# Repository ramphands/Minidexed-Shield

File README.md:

# Minidexed-Shield
A shield for a Raspberry Pi (Model 3) running [Minidexed](https://github.com/probonopd/MiniDexed/)

image of the shield in use

A Pi Pico is used as a Host to Host connection, allowing sequencing via PC or other host device.  Code obtained from [rsta2's "midi_adapter" Pico repo](https://github.com/rsta2/pico)

Please use the minixeded.ini file in this repo as the encoder pinout is different from the stock .ini

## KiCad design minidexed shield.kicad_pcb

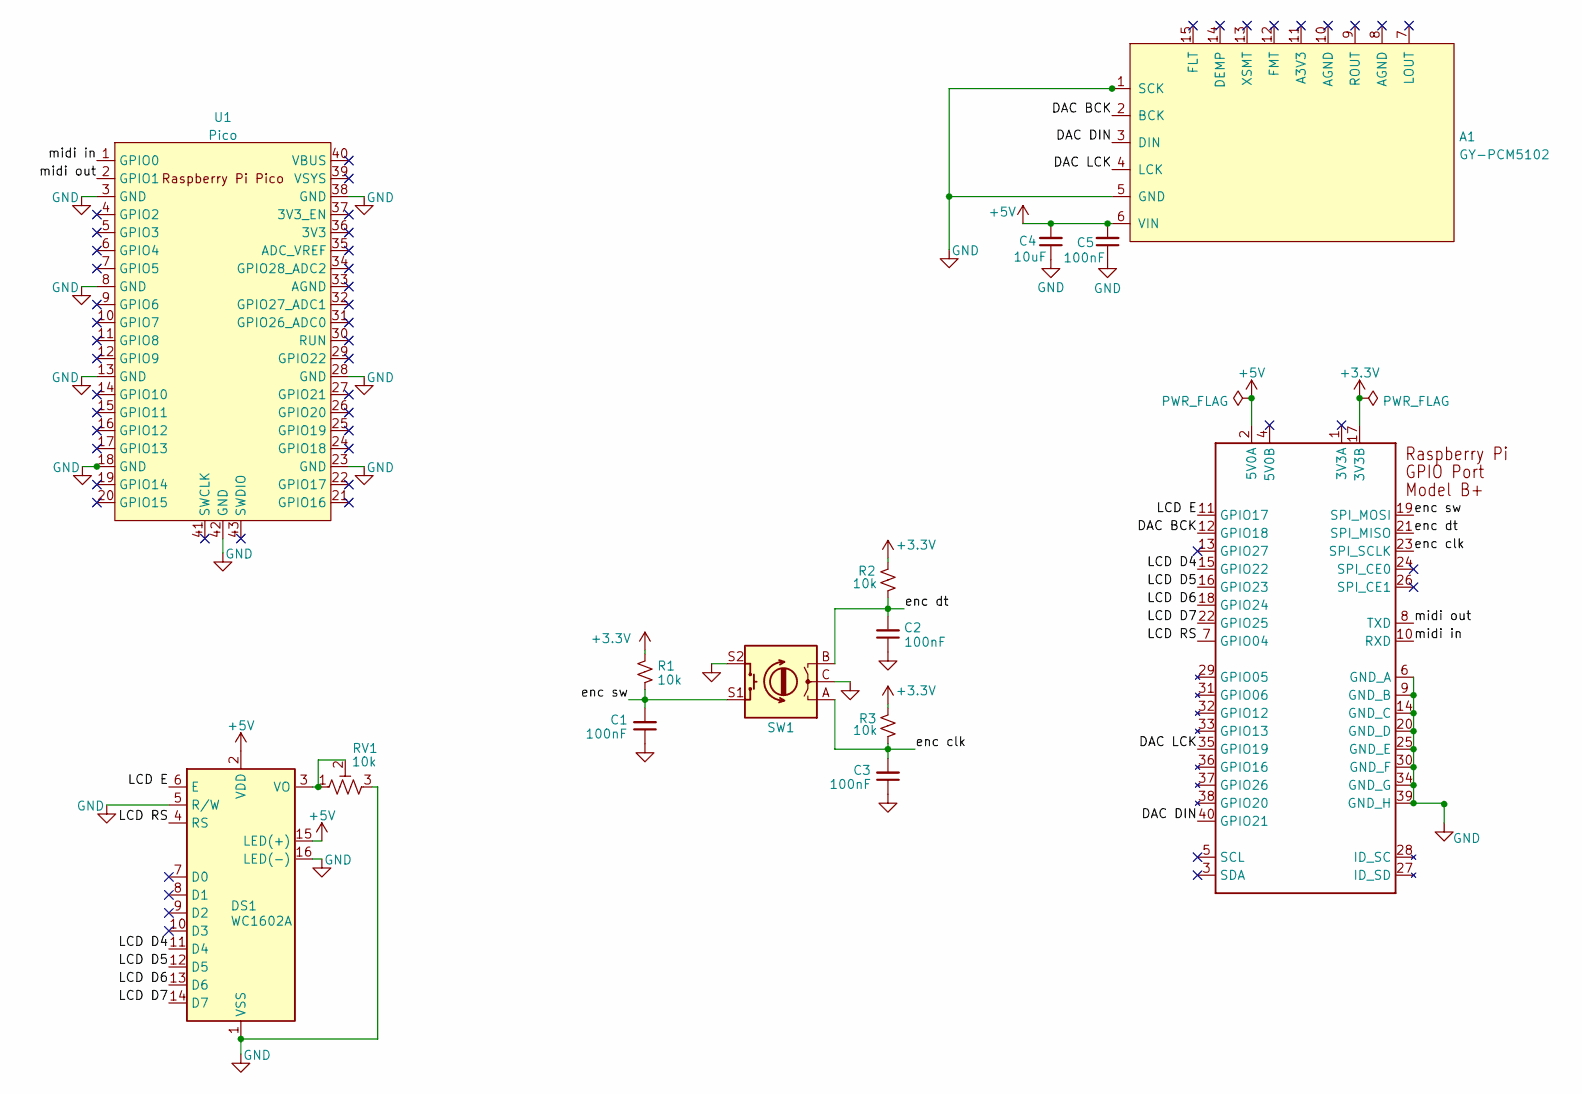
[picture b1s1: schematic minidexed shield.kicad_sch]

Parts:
A1: GY-PCM5102
C1, C2, C3, C5: 100nF; C0805
C4: 10uF; C0805
DS1: WC1602A
R1, R2, R3: 10k; R0603
RV1: 10k; TRIM_3362P-1-103
SW1: RotaryEncoder_Switch; RotaryEncoder_Alps_EC11E-Switch_Vertical_H20mm
U1: Pico; RPi_Pico_SMD_TH
X1: RASPI_BOARD_B+#_E0; RASPI_BOARD_B+_EDGES_3DRILL

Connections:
+3.3V: R1.1, R2.1, R3.2, X1.17 (3V3B)
+5V: A1.6 (VIN), C4.2, C5.2, DS1.2 (VDD), DS1.15 (LED(+)), X1.2 (5V0A)
/DAC BCK: A1.2 (BCK), X1.12 (GPIO18)
/DAC DIN: A1.3 (DIN), X1.40 (GPIO21)
/DAC LCK: A1.4 (LCK), X1.35 (GPIO19)
/LCD D4: DS1.11 (D4), X1.15 (GPIO22)
/LCD D5: DS1.12 (D5), X1.16 (GPIO23)
/LCD D6: DS1.13 (D6), X1.18 (GPIO24)
/LCD D7: DS1.14 (D7), X1.22 (GPIO25)
/LCD E: DS1.6 (E), X1.11 (GPIO17)
/LCD RS: DS1.4 (RS), X1.7 (GPIO04)
/enc clk: C3.2, R3.1, SW1.A, X1.23 (SPI_SCLK)
/enc dt: C2.2, R2.2, SW1.B, X1.21 (SPI_MISO)
/enc sw: C1.2, R1.2, SW1.S1, X1.19 (SPI_MOSI)
/midi in: U1.1 (GPIO0), X1.10 (RXD)
/midi out: U1.2 (GPIO1), X1.8 (TXD)
GND: A1.1 (SCK), A1.5 (GND), C1.1, C2.1, C3.1, C4.1, C5.1, DS1.1 (VSS), DS1.5 (R/W), DS1.16 (LED(-)), RV1.3, SW1.C, SW1.S2, U1.3 (GND), U1.8 (GND), U1.13 (GND), U1.18 (GND), U1.23 (GND), U1.28 (GND), U1.38 (GND), U1.42 (GND), X1.6 (GND_A), X1.9 (GND_B), X1.14 (GND_C), X1.20 (GND_D), X1.25 (GND_E), X1.30 (GND_F), X1.34 (GND_G), X1.39 (GND_H)
unnamed: DS1.3 (VO), RV1.1, RV1.2

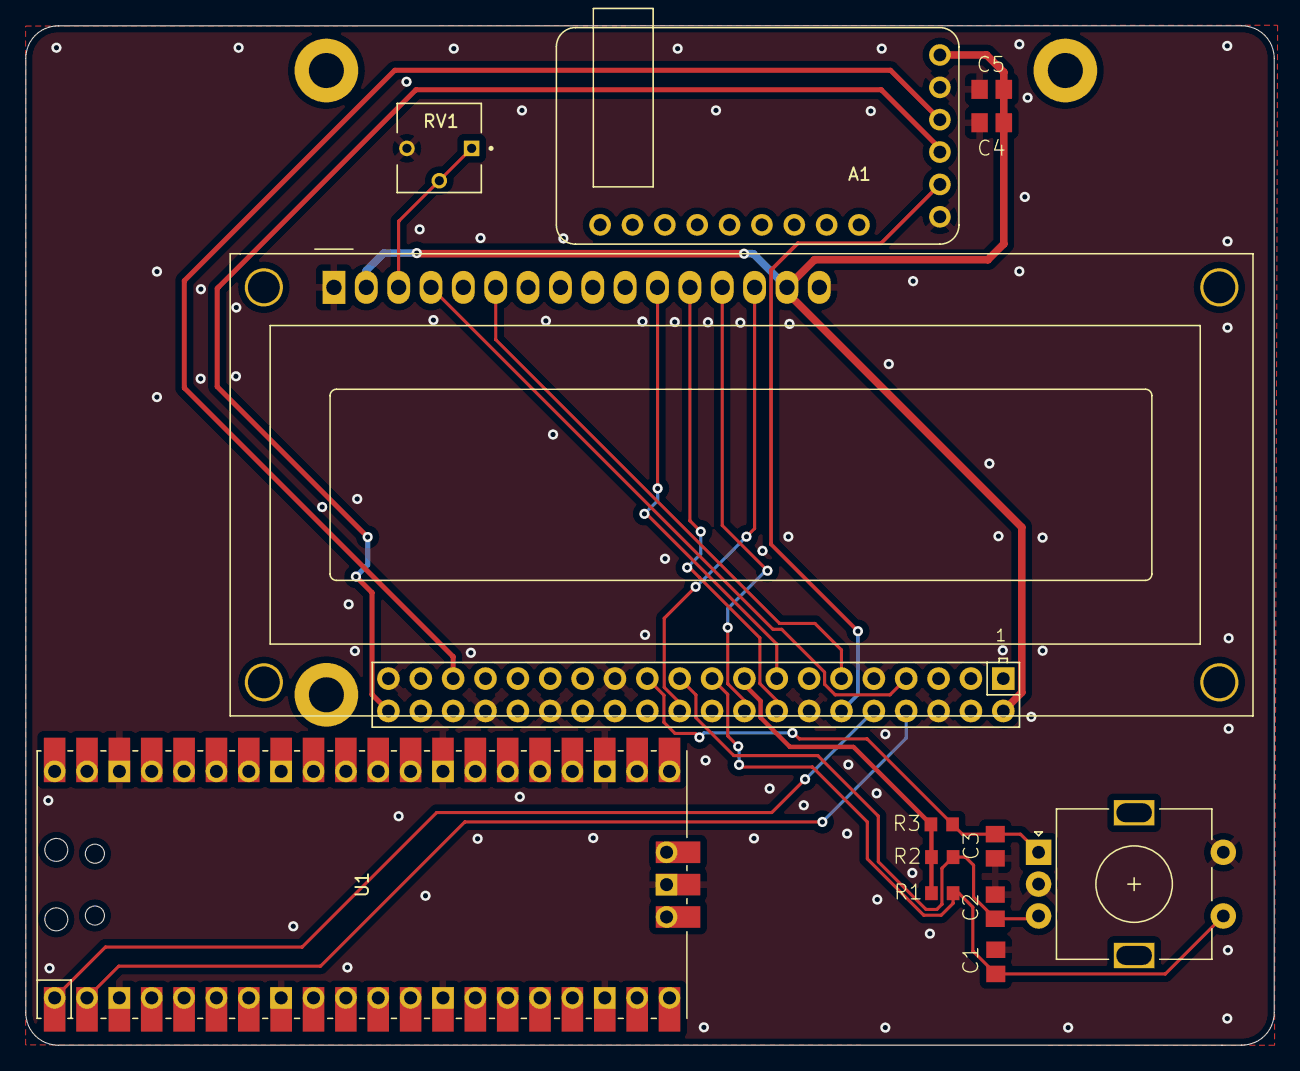
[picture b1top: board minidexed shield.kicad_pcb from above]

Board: 2 copper layers, 98.0 x 80.0 mm, 14 parts (0 on the bottom side), 18 nets.

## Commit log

2022-10-23 Add files via upload
    modified ini file to point to the right GPIO pins
